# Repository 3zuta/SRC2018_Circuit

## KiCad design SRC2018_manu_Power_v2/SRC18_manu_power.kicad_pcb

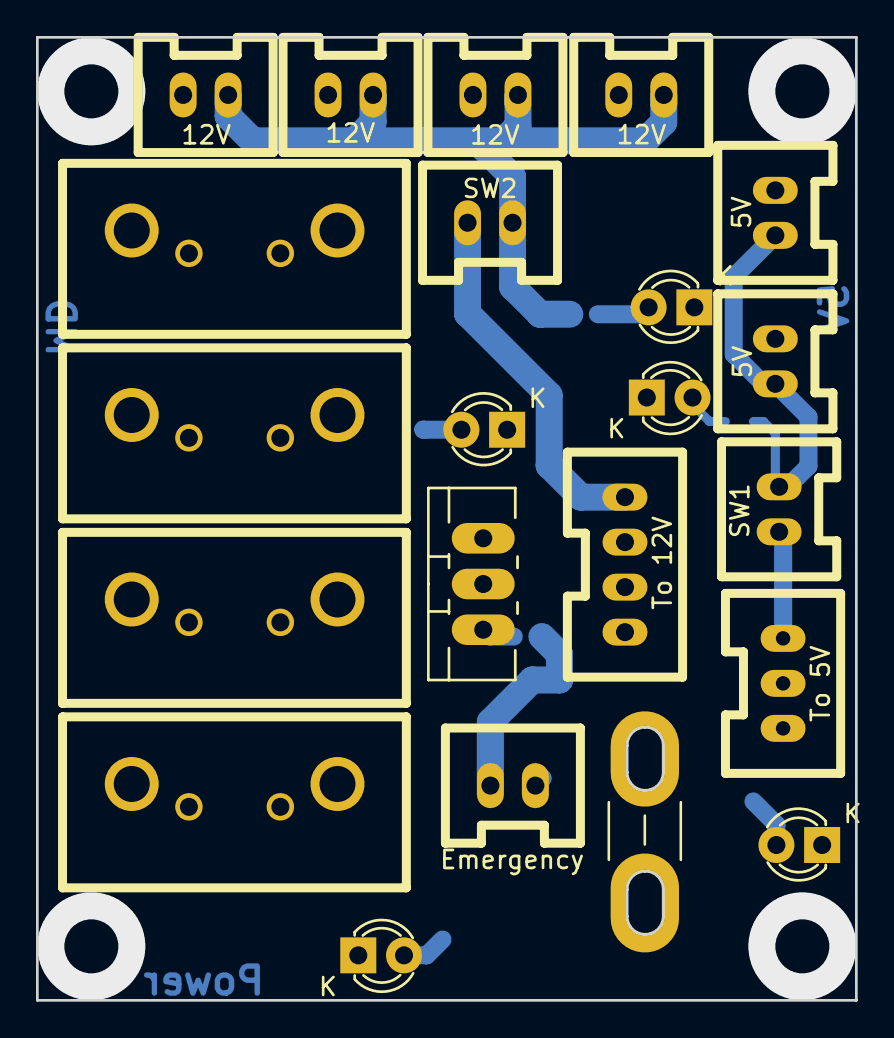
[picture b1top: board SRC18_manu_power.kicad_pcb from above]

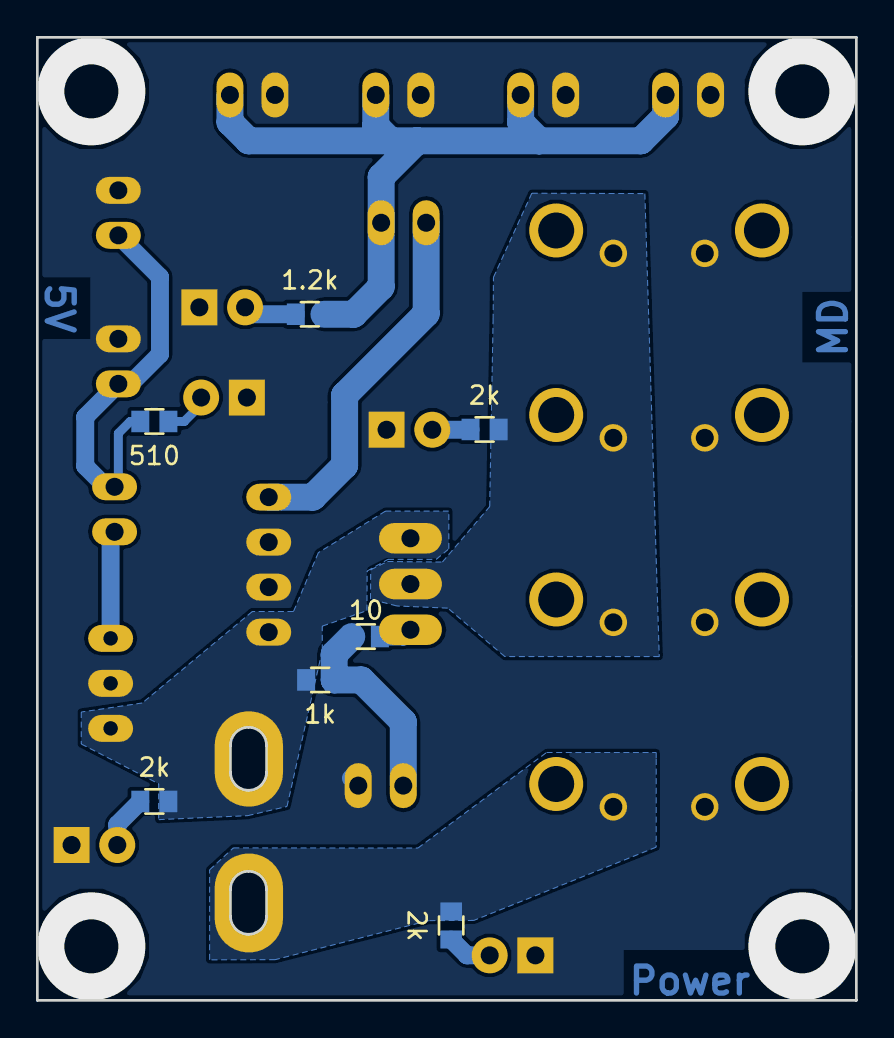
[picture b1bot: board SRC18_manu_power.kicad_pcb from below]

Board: 2 copper layers, 45.5 x 53.5 mm, 29 parts (7 on the bottom side), 15 nets.

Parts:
D1, D2, D3, D4, D5: LED; LED-3MM
F1: FUSE; BladeFuse-Mini
P1: Emergency; XA_2T
P2: To 5V; XA_3T
P3: To 12V; XA_4T
P4, P8, P11: MD_POWER; D3200_2T
P5: POWER_in; D3200_2T
P6, P9: 5V; XA_2T
P7, P10, P12, P13: 12V; XA_2T
Q1: Q_PMOS_GDS; TO-220_Neutral123_Vertical_LargePads
R1: 10; R_0603
R2: 1k; R_0603
R3, R4, R5: 2k; R_0603
R6: 1.2k; R_0603
R7: 510; R_0603
SW1, SW2: SPST; XA_2T

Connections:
+5V: P2.3, SW1.2
+12V: P3.4, SW2.2
+BATT: F1.1, P5.2, R3.1
/5V_SW: P6.2, P9.2, R7.1, SW1.1
/12V_SW: P7.2, P10.2, P12.2, P13.2, R6.1, SW2.1
/ALL_Power: F1.2, P2.1, P3.1, Q1.3, R2.1, R4.1
/MD_POWER: P4.2, P8.2, P11.2, Q1.2, R5.1
GND: D1.1, D2.1, D3.1, D4.1, D5.1, P1.1, P2.2, P3.2, P3.3, P4.1, P5.1, P6.1, P7.1, P8.1, P9.1, P10.1, P11.1, P12.1, P13.1
unnamed: D1.2, R3.2
unnamed: D2.2, R4.2
unnamed: D3.2, R5.2
unnamed: D4.2, R6.2
unnamed: D5.2, R7.2
unnamed: P1.2, R1.2, R2.2
unnamed: Q1.1, R1.1

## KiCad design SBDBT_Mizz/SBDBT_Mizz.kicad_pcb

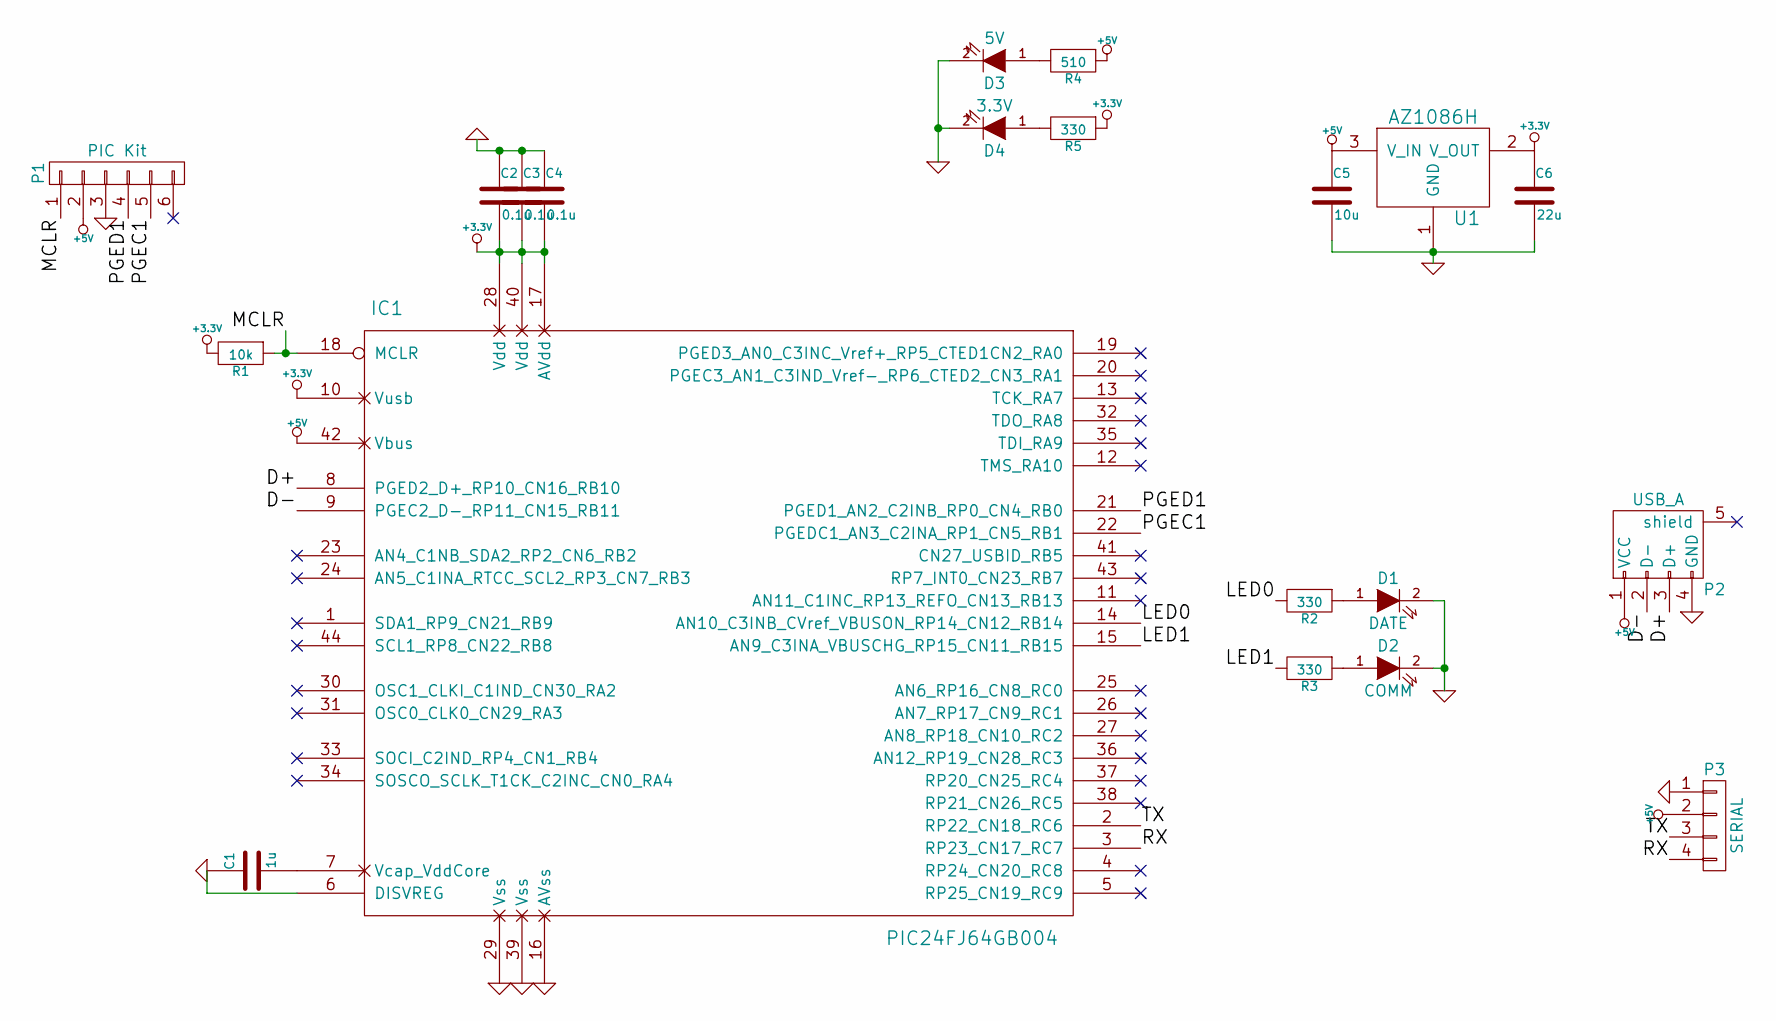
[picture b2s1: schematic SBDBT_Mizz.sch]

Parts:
C1: 1u; C_0603
C2, C3, C4: 0.1u; C_0603
C5: 10u; C_0603
C6: 22u; C_0603
D1: DATE; LED_0603
D2: COMM; LED_0603
D3: 5V; LED_0603
D4: 3.3V; LED_0603
IC1: PIC24FJ64GB004; LQFP-44_10x10mm_Pitch0.8mm
P1: PIC Kit; Pin_Header_Straight_1x06
P2: USB_A
P3: SERIAL; XA_4T
R1: 10k; R_0603
R2, R3, R5: 330; R_0603
R4: 510; R_0603
U1: AZ1086H

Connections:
+3.3V: C2.2, C3.2, C4.2, C6.1, IC1.10 (Vusb), IC1.17 (AVdd), IC1.28 (Vdd), IC1.40 (Vdd), R1.2, R5.1, U1.2 (V_OUT)
+5V: C5.1, IC1.42 (Vbus), P1.2, P2.1 (VCC), P3.2, R4.1, U1.3 (V_IN)
/D+: IC1.8 (PGED2_D+_RP10_CN16_RB10), P2.3 (D+)
/D-: IC1.9 (PGEC2_D-_RP11_CN15_RB11), P2.2 (D-)
/LED0: IC1.14 (AN10_C3INB_CVref_VBUSON_RP14_CN12_RB14), R2.2
/LED1: IC1.15 (AN9_C3INA_VBUSCHG_RP15_CN11_RB15), R3.2
/MCLR: IC1.18 (MCLR), P1.1, R1.1
/PGEC1: IC1.22 (PGEDC1_AN3_C2INA_RP1_CN5_RB1), P1.5
/PGED1: IC1.21 (PGED1_AN2_C2INB_RP0_CN4_RB0), P1.4
/RX: IC1.3 (RP23_CN17_RC7), P3.4
/TX: IC1.2 (RP22_CN18_RC6), P3.3
GND: C1.1, C2.1, C3.1, C4.1, C5.2, C6.2, D1.2 (K), D2.2 (K), D3.2 (K), D4.2 (K), IC1.6 (DISVREG), IC1.16 (AVss), IC1.29 (Vss), IC1.39 (Vss), P1.3, P2.4 (GND), P3.1, U1.1 (GND)
unnamed: C1.2, IC1.7 (Vcap_VddCore)
unnamed: D1.1 (A), R2.1
unnamed: D2.1 (A), R3.1
unnamed: D3.1 (A), R4.2
unnamed: D4.1 (A), R5.2

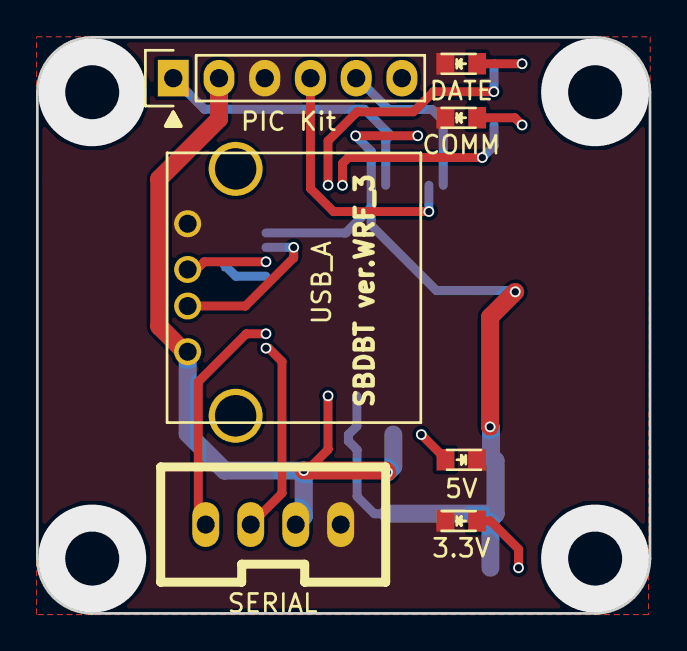
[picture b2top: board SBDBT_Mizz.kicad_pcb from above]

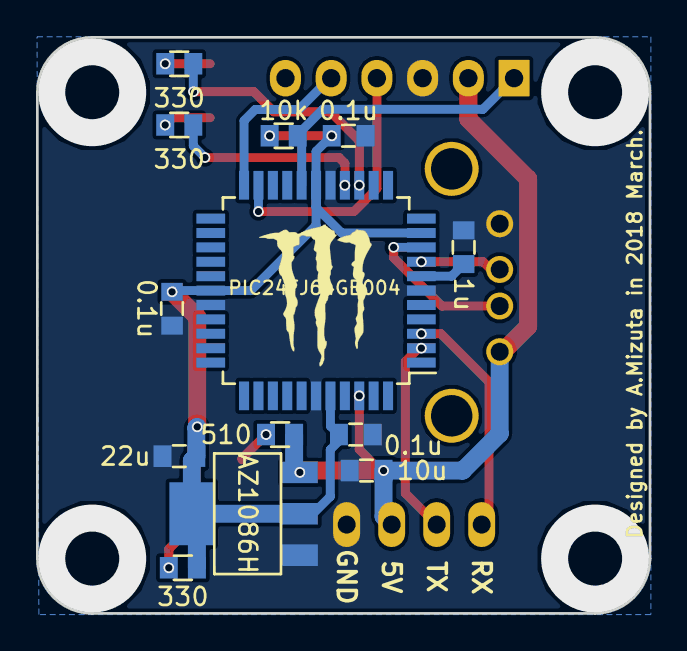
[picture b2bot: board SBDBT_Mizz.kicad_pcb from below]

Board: 2 copper layers, 34.0 x 32.0 mm, 20 parts (13 on the bottom side), 17 nets.

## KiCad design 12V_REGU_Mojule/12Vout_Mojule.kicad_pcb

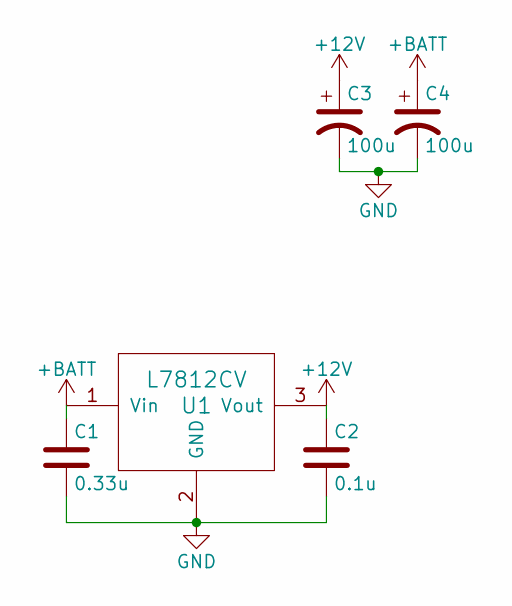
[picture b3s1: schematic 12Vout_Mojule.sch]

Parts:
C1: 0.33u; C_0603
C2: 0.1u; C_0603
C3, C4: 100u; C_Radial_D5_L11_P2
U1: L7812CV; TO-220_Neutral123_Horizontal_MountedFromLS_LargePads

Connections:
+12V: C2.1, C3.1, U1.3 (Vout)
+BATT: C1.1, C4.1, U1.1 (Vin)
GND: C1.2, C2.2, C3.2, C4.2, U1.2 (GND)

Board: 2 copper layers, 5 parts (5 on the bottom side), 3 nets, no tracks yet.

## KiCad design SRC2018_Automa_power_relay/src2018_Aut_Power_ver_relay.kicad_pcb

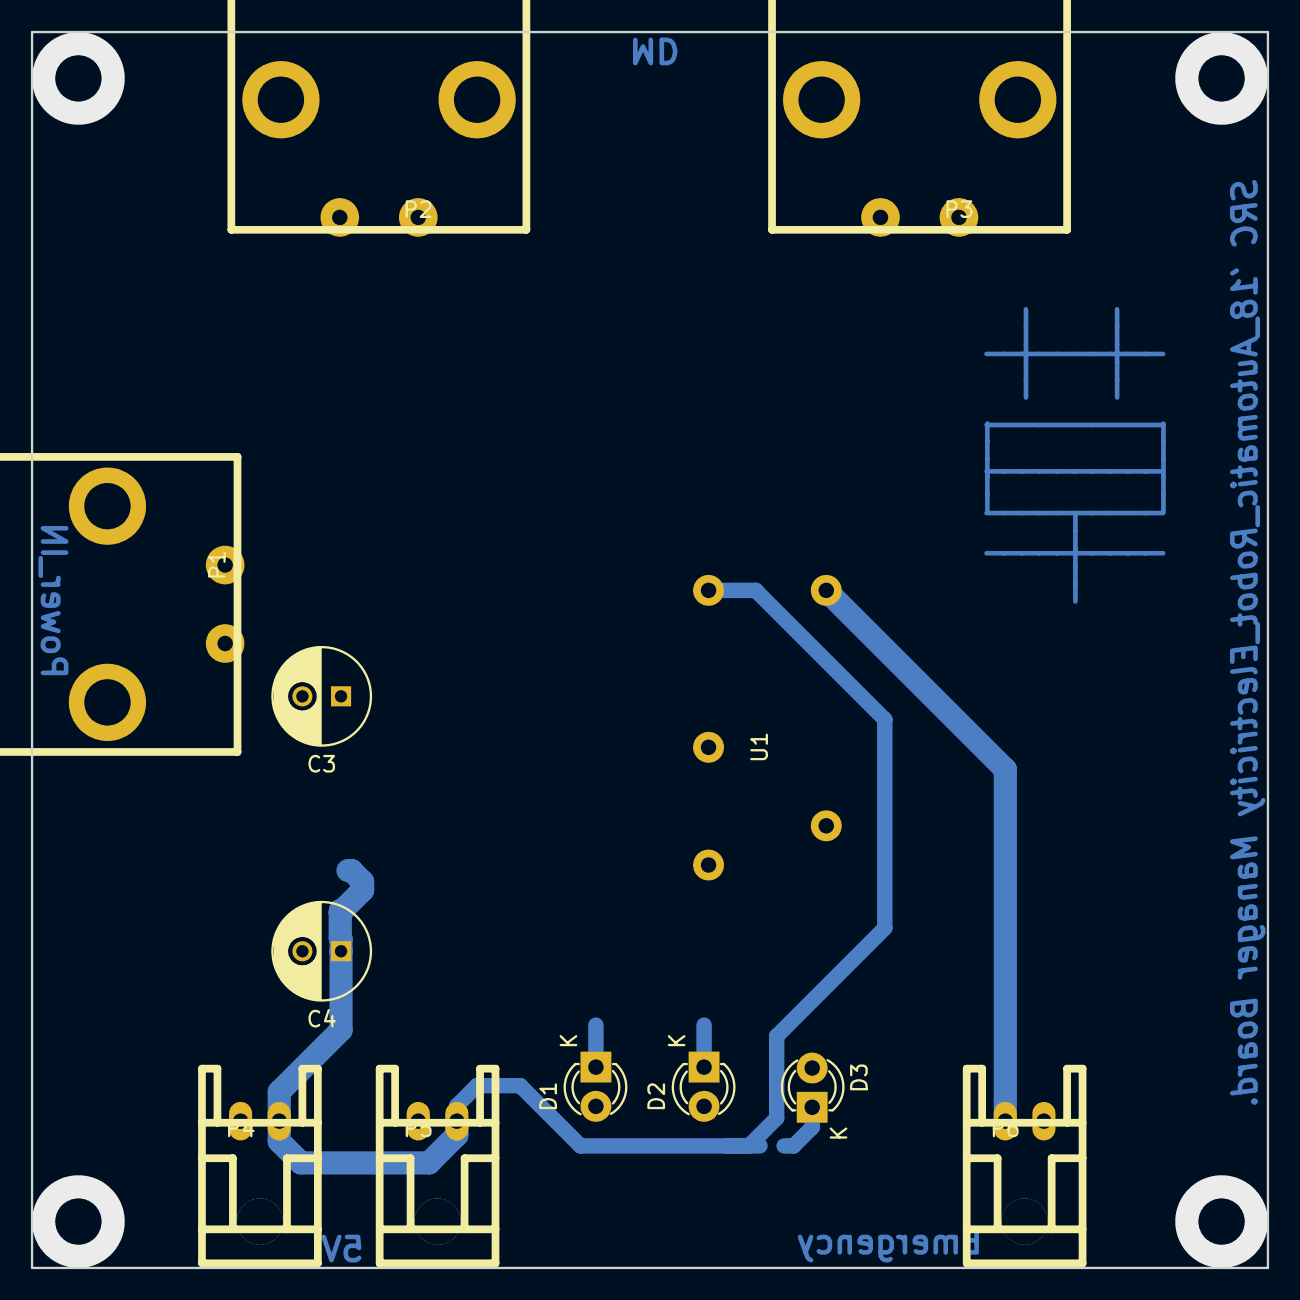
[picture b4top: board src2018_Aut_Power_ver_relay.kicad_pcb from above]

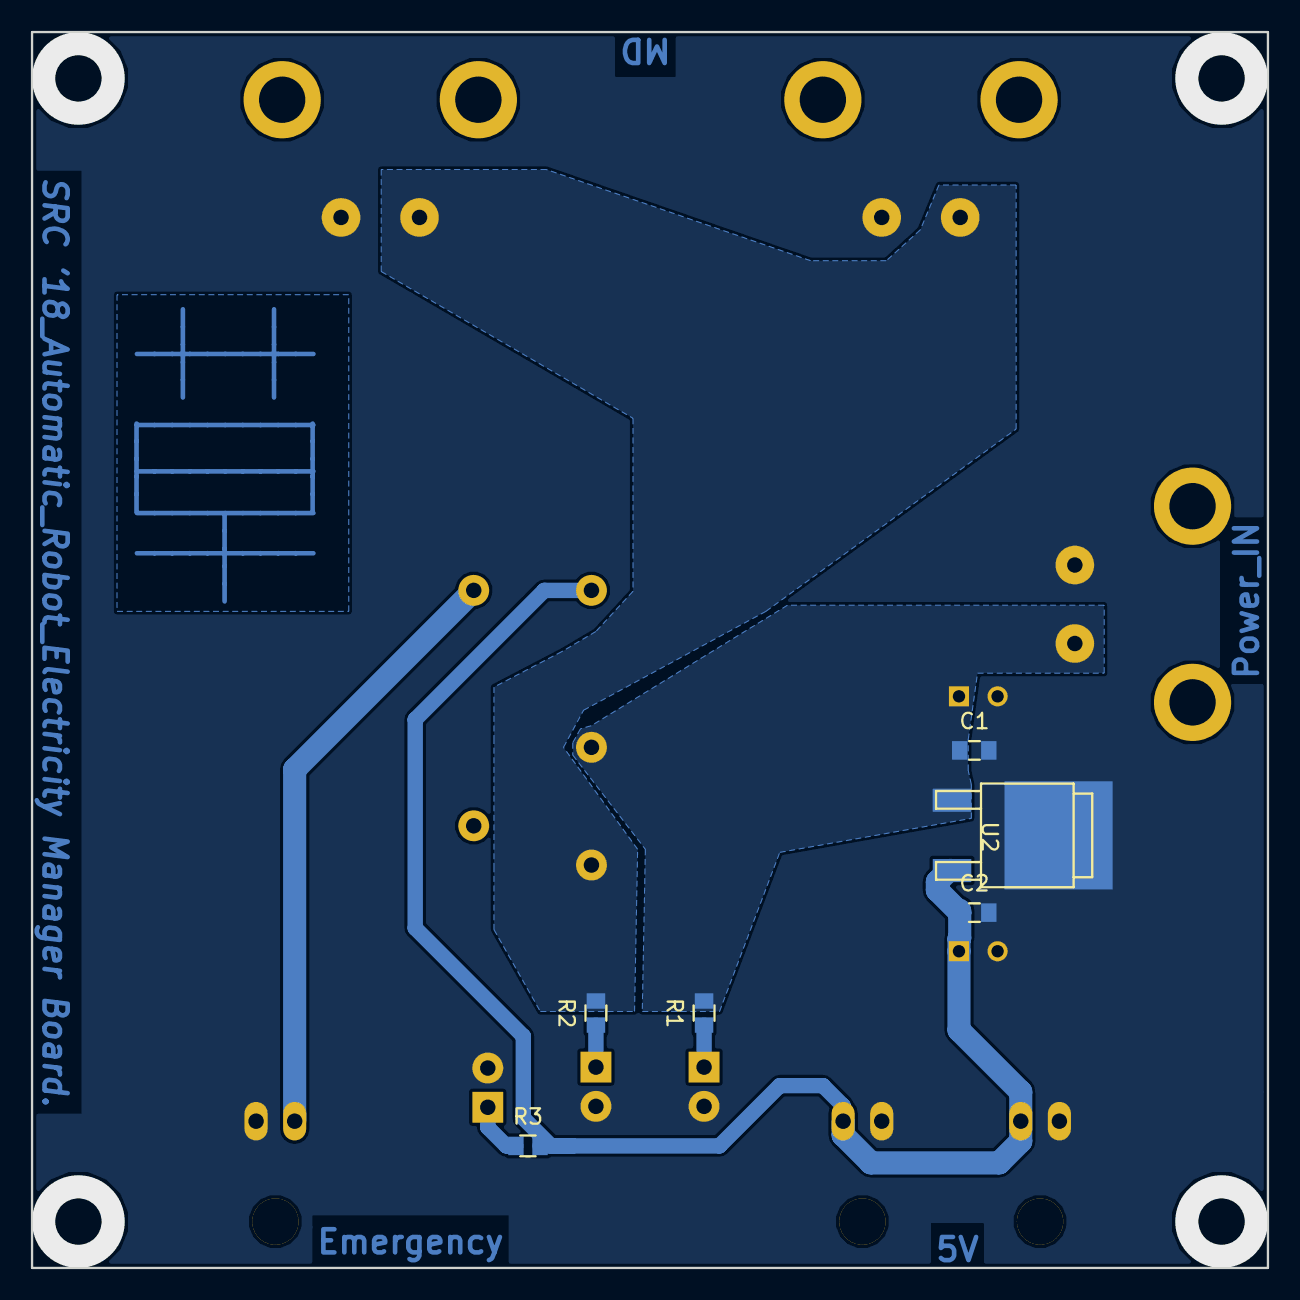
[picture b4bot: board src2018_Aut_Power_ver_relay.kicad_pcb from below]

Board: 2 copper layers, 80.0 x 80.0 mm, 18 parts (6 on the bottom side), 8 nets.

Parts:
C1, C2: 0.1u; C_0603
C3, C4: 100u; C_Radial_D6.3_L11.2_P2.5
D1, D2, D3: LED; LED-3MM
P1: Power_IN; D-3200S_2L
P2, P3: MD_OUT; D-3200S_2L
P4, P5: 5V_OUT; XA_2LC
P6: Emergency; XA_2LC
R1, R2: 1k; R_0603
R3: 510; R_0603
U1: LQ_Relay
U2: 7805; SOT-428

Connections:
+5V: C2.1, C4.1, P4.2, P5.2, R3.2, U1.2, U2.3
+BATT: C1.1, C3.1, P1.2, R1.2, U1.3, U2.1
/MD_OUT: P2.2, P3.2, R2.2, U1.4
GND: C1.2, C2.2, C3.2, C4.2, D1.2, D2.2, D3.2, P1.1, P2.1, P3.1, P4.1, P5.1, P6.2, U2.2
unnamed: D1.1, R1.1
unnamed: D2.1, R2.1
unnamed: D3.1, R3.1
unnamed: P6.1, U1.1

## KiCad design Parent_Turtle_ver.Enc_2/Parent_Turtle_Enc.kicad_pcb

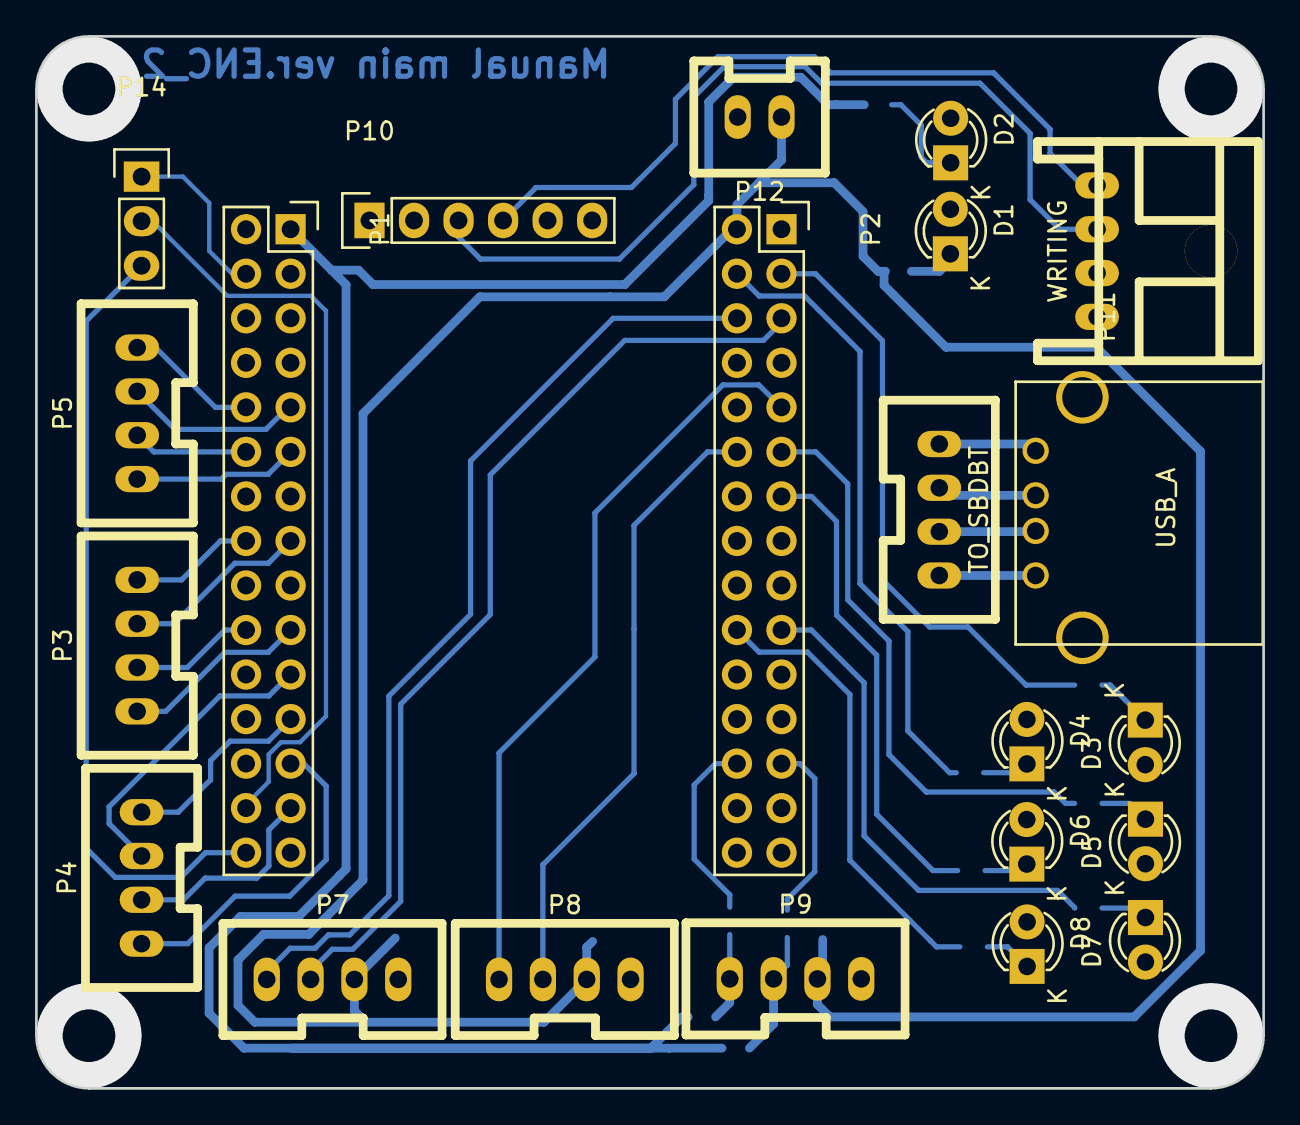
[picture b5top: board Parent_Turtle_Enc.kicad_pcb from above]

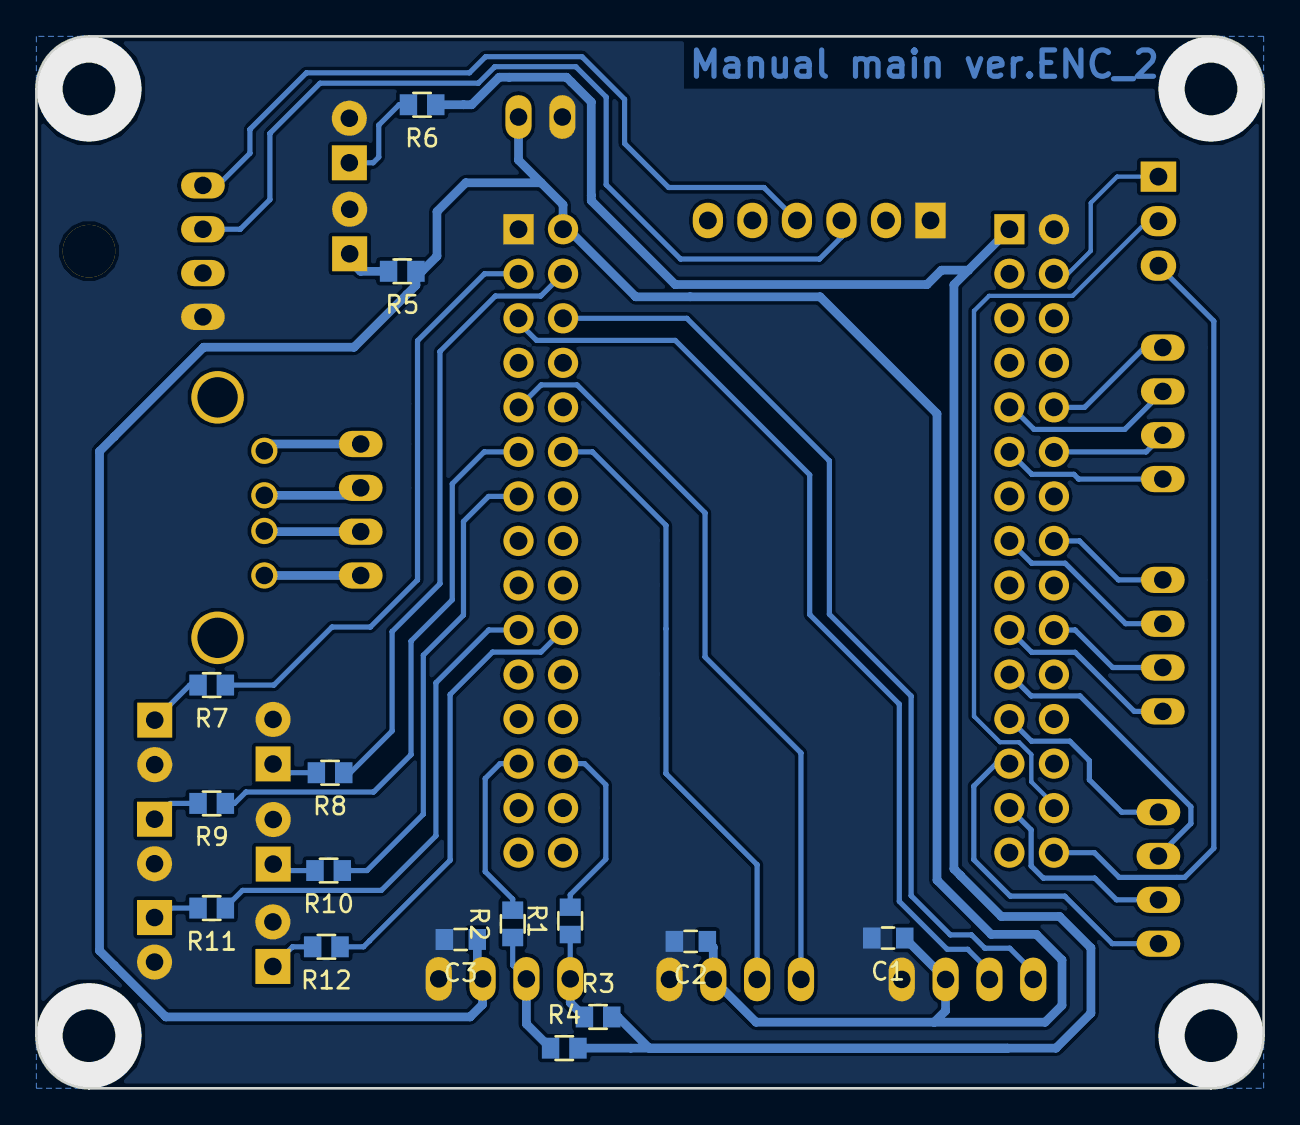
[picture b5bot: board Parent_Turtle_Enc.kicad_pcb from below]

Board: 2 copper layers, 70.0 x 60.0 mm, 37 parts (15 on the bottom side), 46 nets.

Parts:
C1, C2, C3: 0.1u; C_0603
D1, D2, D3, D4, D5, D6, D7, D8: LED; LED-3MM
P1, P2: CONN_02X15; Socket_Strip_Straight_2x15
P3: MD0_1; XA_4T
P4: MD2_3; XA_4T
P5: MD4_5; XA_4T
P7: SERIAL0; XA_4T
P8: SERIAL1; XA_4T
P9: ENC0; XA_4T
P10: WRITING_IN; Socket_Strip_Straight_1x06
P11: WRITING; XA_4LC
P12: 5V_in; XA_2T
P13: USB_A
P14: PWM; Pin_Header_Straight_1x03
P15: TO_SBDBT; XA_4T
R1, R2: 100; R_0603
R3, R4: 1k; R_0603
R5: 510; R_0603
R6, R7, R8, R9, R10, R11, R12: 330; R_0603

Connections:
+3.3V: P1.1, R3.2, R4.2, R6.1
+5V: C1.1, C2.1, C3.1, P2.2, P7.2, P8.2, P9.2, P12.2, R5.1
/A0: P1.9, P5.2
/A1: P1.10, P5.1
/A2: P1.11, P5.4
/A3: P1.12, P5.3
/A6: P1.15, P3.2
/A7: P1.16, P3.1
/A15: P2.13, R10.1
/B0: P1.19, P3.4
/B1: P1.20, P3.3
/B6: P2.5, P7.3
/B7: P2.6, P7.4
/B8: P2.3, R7.1
/B9: P2.4, R8.1
/B10: P1.28, P14.2
/B11: P1.30, P14.3
/C8: P2.19, R11.1
/C9: P2.20, R12.1
/CLK: P10.3, P11.3
/D2: P2.11, R9.1
/D5: P2.12, P8.3
/D6: P2.9, P8.4
/D12: P2.25, R2.2
/D13: P2.26, R1.2
/D+: P13.3, P15.3
/D-: P13.2, P15.2
/DIO: P10.4, P11.4
/E6: P1.4, P14.1
/E8: P1.21, P4.2
/E10: P1.23, P4.1
/E12: P1.25, P4.4
/E14: P1.27, P4.3
/GND_USB: P13.4, P15.4
/Vcc: P13.1, P15.1
GND: C1.2, C2.2, C3.2, D1.2, D2.2, D3.2, D4.2, D5.2, D6.2, D7.2, D8.2, P1.2, P2.1, P7.1, P8.1, P9.1, P10.1, P11.1, P12.1
unnamed: D1.1, R5.2
unnamed: D2.1, R6.2
unnamed: D3.1, R7.2
unnamed: D4.1, R8.2
unnamed: D5.1, R9.2
unnamed: D6.1, R10.2
unnamed: D7.1, R11.2
unnamed: D8.1, R12.2
unnamed: P9.3, R2.1, R4.1
unnamed: P9.4, R1.1, R3.1

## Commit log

2018-08-22 will be used circuit board.
2018-08-22 Add circuit project and production file.
2018-09-05 Add Automatic Robot's Power Manager Board's Project.
2018-09-16 Add SRC2018_Manual Robot's power circuit.
2019-10-02 push復活してくれ
